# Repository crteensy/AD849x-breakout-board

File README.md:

AD849x-breakout-board
=====================

Breakout board for the AD849x thermocouple amplifier ICs

Hackaday project page: http://hackaday.io/project/1758-AD849x-breakout-board

Shared on OSH Park: https://oshpark.com/shared_projects/QypWyps2

examples/pedvideContinuousSingleEnded.ino is a small example to run on a Teensy 3.0 or 3.1, written for teensyduino and pedvide's ADC library

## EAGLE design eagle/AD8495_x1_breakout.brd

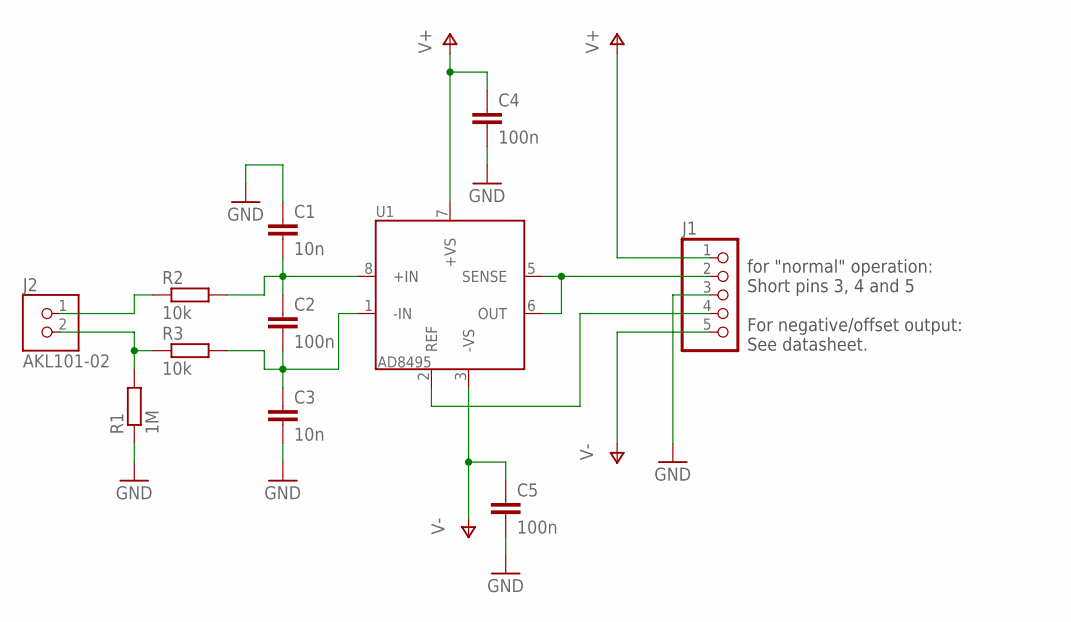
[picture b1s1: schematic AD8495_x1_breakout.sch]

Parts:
C1, C3: 10n; C0805
C2, C4, C5: 100n; C0805
J1: PINHD-1X5; 1X05
J2: AKL101-02
R1: 1M; R0805
R2, R3: 10k; R0805
U1: AD8495RMZ; MS_MSOP8

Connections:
GND: C1.1, C3.2, C4.2, C5.2, J1.3, R1.1
unnamed: C2.2, C3.1, R3.2, U1.1 (-IN)
unnamed: C1.2, C2.1, R2.2, U1.8 (+IN)
unnamed: J2.2, R1.2, R3.1
unnamed: J2.1, R2.1
unnamed: J1.4, U1.2 (REF)
unnamed: J1.2, U1.5 (SENSE), U1.6 (OUT)
V+: C4.1, J1.1, U1.7 (+VS)
V-: C5.1, J1.5, U1.3 (-VS)

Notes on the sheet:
for "normal" operation: Short pins 3, 4 and 5 For negative/offset output: See datasheet.

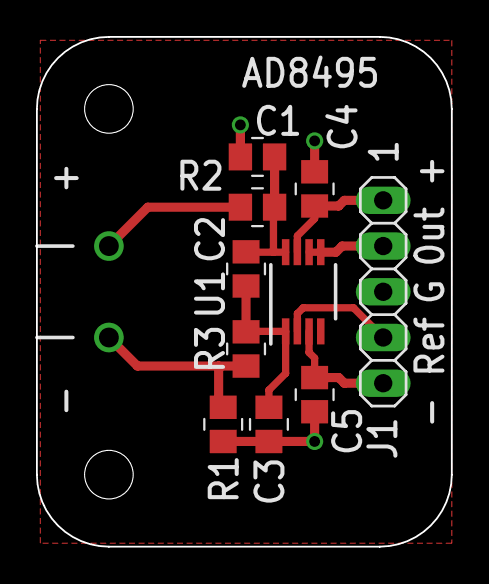
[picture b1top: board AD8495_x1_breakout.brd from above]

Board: 2 copper layers, 23.1 x 28.3 mm, 11 parts (0 on the bottom side), 9 nets.

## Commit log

2014-07-12 Update README.md
    Added links
2014-07-12 Added eagle and OCH Park CAM files
2014-08-23 Create pedvideContinuousSingleEnded.ino
    Added example sketch for teensyduino, with pedvide's ADC library, running on a Teensy 3.0 or 3.1
2014-08-23 Update README.md
    included example description
